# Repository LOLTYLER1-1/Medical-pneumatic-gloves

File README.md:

# 医用气动辅助手套 (Medical Pneumatic Assistive Glove)

> 基于 **正点原子领航者 V3.9 ZYNQ7020** + **7" 800×480 触摸 LCD** 的手指被动康复训练装置
> PL(FPGA) + PS(ARM) 协同实现，不依赖外部 MCU
> 创建：2026-05-11 ｜ 最新修订：2026-08-16（台架联调打通）

---

## 项目简介

面向脑卒中后手指屈曲挛缩、神经损伤患者的手指 **被动屈伸训练** 装置：

- **摸左半屏** → 气泵加压到设定值（默认 50 kPa）自动停止，手套气室鼓胀带动手指屈曲
- **摸右半屏** → 泄气阀打开，自然回弹松手
- LCD 实时显示压力数值（`XXX.XX KPA` 大字）、状态色条、压力条
- **三层安全保护**：PL 端纯组合逻辑硬件强切（≥80 kPa 泵阀双断）、板载 KEY1 急停、
  传感器故障检测（通信失败 2~3 秒内蜂鸣 + 自动泄气锁定）
- 泄气阀选用 **常开型 (NO)**：断电自动泄压，fail-safe

### 工作原理一句话

```
摸 LCD → GT911(PS 端 EMIO 软件 IIC) → ZYNQ7020 → PCB 驱动板 → 气泵/泄气阀 → 手套气室
                                        ↑                    │
                                        └── XGZP6857D 气压传感器 (IIC 闭环反馈) ──┘
```

📹 **演示视频**：
- [`无气压传感器版实验演示_2026-09-04.mp4`](./无气压传感器版实验演示_2026-09-04.mp4)（无气压传感器版本实验，2026-09-04）
- [`简易版实验结果演示.mp4`](./简易版实验结果演示.mp4)（仿真压力模式，气球抓握演示，2026-08）
🖼️ **定稿电路图**：[`最终电路图.png`](./最终电路图.png)

---

## 当前状态（2026-08-16）

| 项 | 状态 |
|---|---|
| PL 端 13 个 Verilog 模块 + XDC + 比特流 | ✅ 完成并上板验证 |
| GT911 触摸（复位时序根因已修复） | ✅ 左右半屏充/泄请求完好 |
| PS 端 Vitis 应用（EMIO / DCC 日志 / 心跳 LED） | ✅ 完成 |
| 驱动板 PCB（立创EDA 工程 + Gerber，三重验证） | ✅ 2026-07-30 完成 |
| 台架联调（仿真压力模式气球演示） | ✅ 2026-08-04 成功 |
| 真实压力闭环 | ⏳ 等重买 XGZP6857D **IIC 数字版**（旧传感器疑似焊接烫死），到手后 `SIM_PRESSURE` 改 0 |
| 遗留硬件 | ⏳ 12V GND 与 ATK GND 需并 2~3 根地线（治地弹负尖峰）；ULN2803 COM 接 12V 待确认 |

---

## 仓库结构

```
medical project/
├─ README.md                        ← 本文件
├─ 最终电路图.png                    ← 定稿电路图 (4400×3300, 全元件覆盖)
├─ 简易版实验结果演示.mp4             ← 台架演示视频 (2026-08)
├─ 无气压传感器版实验演示_2026-09-04.mp4 ← 无气压传感器版实验视频 (2026-09-04)
├─ lcd_image.coe                    ← LCD 中心图片初始化文件 (200×175 RGB565)
│
├─ 01_思维导图/项目思维导图.md         ← 系统全景、里程碑、开发顺序
├─ 02_原理图/
│   ├─ 系统原理图.md                 ← 框图/气路/电气连接/引脚表/台架联调记录
│   └─ gen_final_circuit.py         ← 定稿电路图生成脚本 (改后重跑出新图)
│
├─ 03_元件清单/
│   ├─ 元件采购清单.md               ← 采购方案与注意事项
│   ├─ 最终元件清单_2026-07-21.md/.png  ← ★ 权威 BOM
│   ├─ 淘宝直搜词清单_2026-07-22.md/.png ← 下单搜索关键词
│   └─ XGZP6857D_引脚图.png          ← 传感器引脚辨别图
│
├─ 05_FPGA_PL/                      ← PL 端 Verilog (Vivado 2020.2)
│   ├─ 00_top/ ~ 12_pressure_model/ ← 13 个模块, 每个都有干净版+逐行注释教学版
│   ├─ constraints/medical_glove.xdc
│   ├─ sim/                         ← Testbench + Python 事务级/比特级仿真脚本
│   └─ README.md                    ← Vivado 工程重建步骤 (IP/BD 配置)
│
├─ 06_PS/                           ← PS 端 ARM 软件 (Vitis 2020.2)
│   ├─ system_top.xsa               ← 硬件移交文件 (含比特流)
│   └─ VITIS/medical_glove_app/src/ ← 应用源码 (main/ft5206/touch/myiic/emio_iic_cfg)
│
└─ 07_PCB/                          ← 驱动板 PCB (立创EDA 专业版)
    ├─ 医用手套驱动板.epro            ← 完整工程, 可直接打开/编辑/下单
    ├─ 医用手套驱动板_gerber.zip       ← 打板生产文件 (2层 90×68mm 全直插)
    ├─ 验证报告.md / 下单与使用指南.md
    └─ gen_pcb.py 等                 ← PCB 自动生成与校验脚本
```

---

## 硬件连接要点（ATK MODULE U4 排针，唯一外接点）

ATK 口丝印是历史名称（UART 模块用），实际就是 4 个普通 FPGA IO：

| ATK 丝印 | FPGA 引脚 | 本项目信号 |
|---|---|---|
| LED | N15 | 气压传感器 SCL |
| KEY | G14 | 气压传感器 SDA |
| RXD | T19 | 气泵驱动 (→100R→IRLZ44N 栅极) |
| TXD | J15 | 泄气阀驱动 (→ULN2803 IN1) |
| GND | — | 共地（**12V 适配器负极必须接这里，并 2~3 根地线**） |
| VCC | — | +5V（仅传感器/上拉电源，禁带泵阀） |

板载资源（免外接）：LED0=H15 状态/心跳，KEY1=K16 急停，蜂鸣器=M14 告警，KEY_RST=N16 复位。

---

## 快速开始

1. 读文档：[思维导图](./01_思维导图/项目思维导图.md) → [系统原理图](./02_原理图/系统原理图.md) → [元件清单](./03_元件清单/最终元件清单_2026-07-21.md)
2. PL 重建：按 [`05_FPGA_PL/README.md`](./05_FPGA_PL/README.md) 新建 Vivado 2020.2 工程
   （器件 `xc7z020clg400-2`，需配 `clk_wiz_0` + `lcd_image_rom` 两个 IP + PS7 Block Design）
3. PS 重建：Vitis 2020.2 导入 `06_PS/system_top.xsa`，新建应用加入 `06_PS/VITIS/medical_glove_app/src/`
4. 无传感器演示：`medical_glove_top.v` 中 `SIM_PRESSURE=1`（仿真压力模型顶替传感器）；
   传感器到位后改 0 恢复真实闭环
5. 打板：`07_PCB/医用手套驱动板_gerber.zip` 直接上传嘉立创下单

---

## 安全声明

⚠️ 本项目为 **学习实验作品**，不是医疗器械，禁止替代正规康复治疗。
任何穿戴测试前，必须先用气球/瓶罐做负载验证；压力硬上限 80 kPa 由 PL 纯组合逻辑强切，
泄气阀断电自动打开（fail-safe）。

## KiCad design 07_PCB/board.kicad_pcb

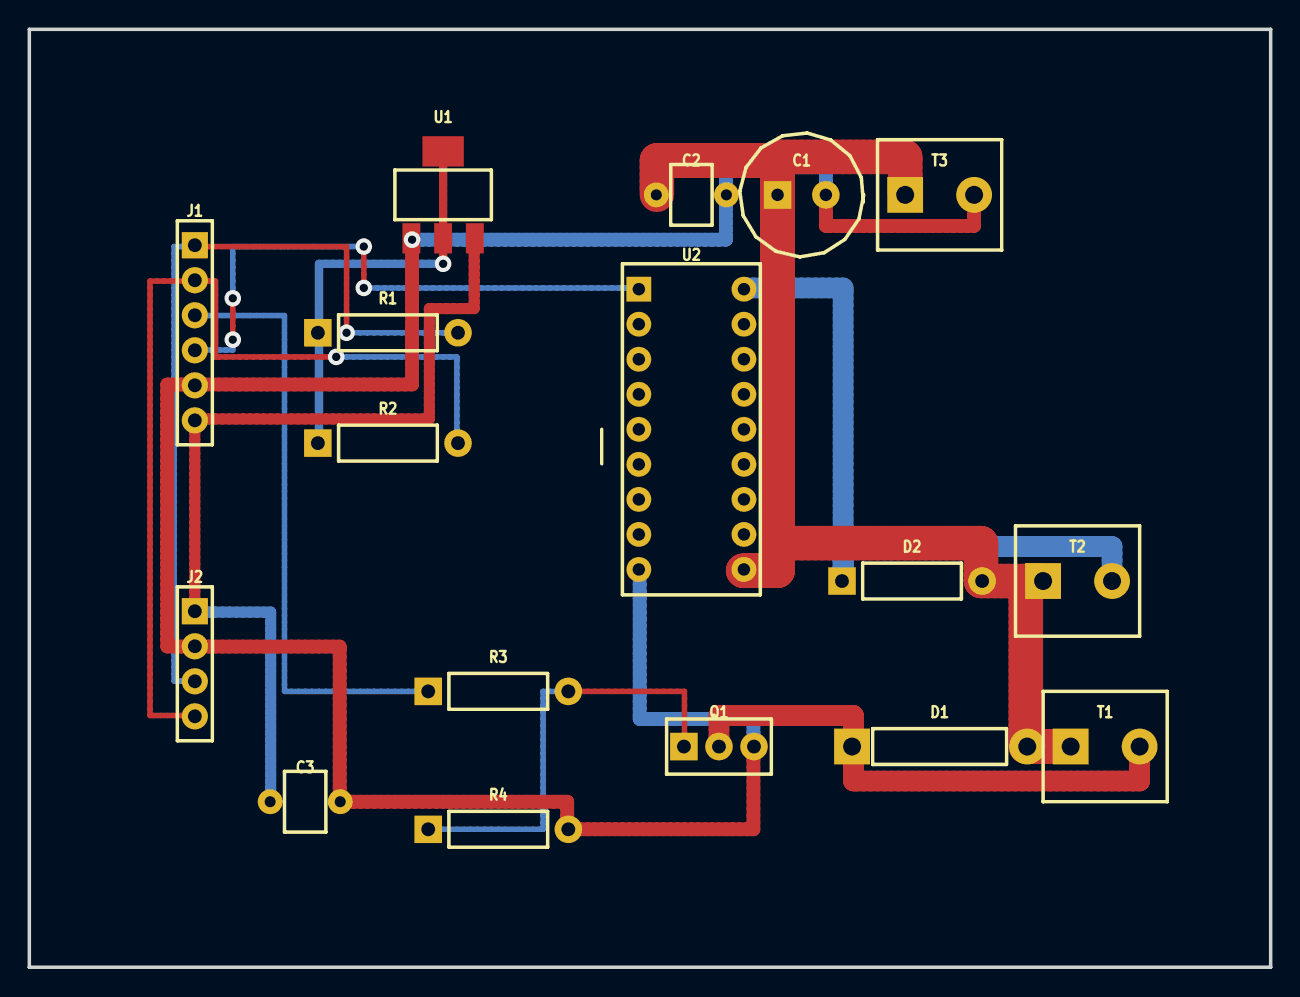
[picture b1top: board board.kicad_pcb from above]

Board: 2 copper layers, 90.0 x 68.0 mm, 17 parts (0 on the bottom side), 11 nets.

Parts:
C1: ELEC
C2, C3: CER
D1: DO201AD
D2: DO41
J1: HDR6
J2: HDR4
Q1: TO220
R1, R2, R3, R4: AXIAL
T1, T2, T3: KF301
U1: SOT223
U2: DIP18

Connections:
+3.3V: R1.1, R2.1, U1.2, U1.4
+5V: C3.1, J1.6, J2.1, U1.3
+12V: C1.1, C2.1, D1.2, D2.2, T1.1, T2.1, T3.1, U2.10
GATE: Q1.1, R3.2, R4.1
GND: C1.2, C2.2, C3.2, J1.5, J2.2, Q1.3, R4.2, T3.2, U1.1, U2.9
PUMP: J1.3, R3.1
PUMP_D: D1.1, Q1.2, T1.2
SCL: J1.1, J2.3, R1.2
SDA: J1.2, J2.4, R2.2
VALVE: J1.4, U2.1
VALVE_OUT: D2.1, T2.2, U2.18

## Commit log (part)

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2026-05-11 初始化项目：添加思维导图、原理图、元件清单等
